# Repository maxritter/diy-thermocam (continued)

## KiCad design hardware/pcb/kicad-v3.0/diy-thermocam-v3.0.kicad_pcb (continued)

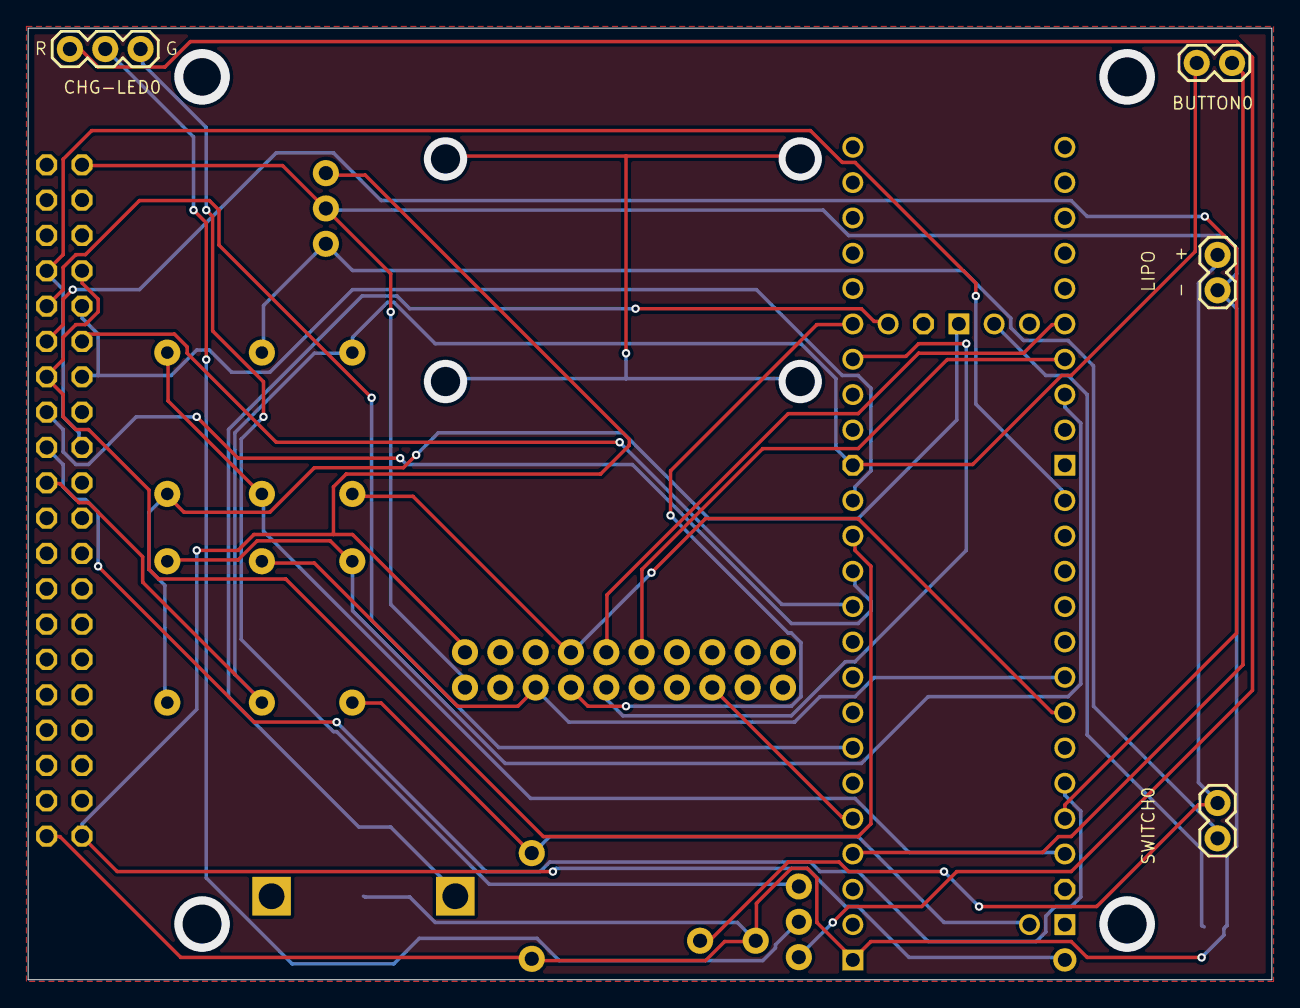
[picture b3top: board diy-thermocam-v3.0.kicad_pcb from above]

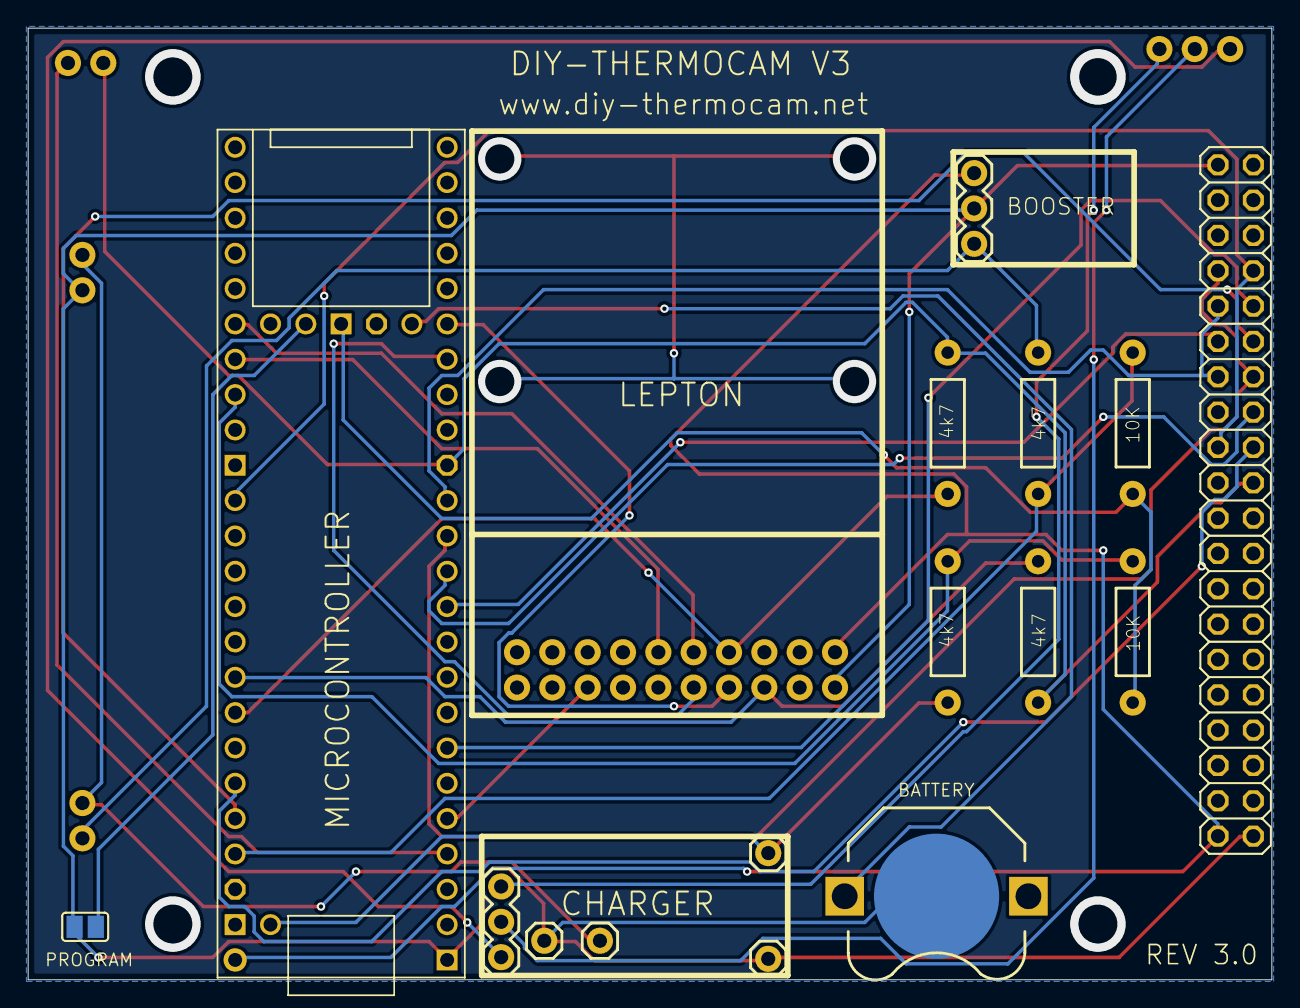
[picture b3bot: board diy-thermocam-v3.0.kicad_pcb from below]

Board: 2 copper layers, 89.4 x 68.4 mm, 21 parts (16 on the bottom side), 30 nets.

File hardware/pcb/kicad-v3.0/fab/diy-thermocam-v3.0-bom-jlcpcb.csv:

Comment,Designator,Footprint,LCSC Part #
BATTCON_12MM_PTH,BAT0,BATTCON_12MM_PTH,
1X03,BOOSTER0,1X03,
M02PTH,BUTTON0,1X02,
M02PTH,BUTTON1,1X02,
1X03,CHG-LED0,1X03,
2X10_NOSILK,J2,2X10_NOSILK,
M01PTH,JP1,1X01,
M01PTH,"JP2,JP3,JP4",1X01,
1X03,LASER1,1X03,
2X20,LCD-HEADER0,2X20,
SJ,PROGRAM0,SJ,
4k7,"R1,R3,R4,R6",AXIAL-0.4,
10K,"R2,R5",AXIAL-0.4,
M02PTH,SWITCH0,1X02,
TEENSY41-E,U$2,TENNSY41-E,C2337

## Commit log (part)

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2021-06-26 Inner.png: added
2021-06-26 index.md: updated image in sections
2021-06-26 Inner_Trans.png: added
2021-06-26 index.md: updated content in sections
2021-06-26 index.md: changed
2021-06-26 thermal-images.md: updated content in sections
2021-06-26 index.md: updated title in seo
2021-06-26 index.md: updated description in seo
2021-06-26 index.md: updated value in extra
2021-06-26 build-your-own.md: updated markdown_content
2021-06-27 manual.md: added. docs.yml: added page src/pages/docs/manual.md
2021-06-27 manual.md: changed
2021-06-27 manual.md: added
2021-06-27 manual.md: removed
2021-06-27 index.md: added
2021-06-27 usb-protocol.md: removed
2021-06-27 manual: removed
2021-06-27 site-metadata.json: updated nav_links in header
2021-06-27 site-metadata.json: updated style in nav_links
2021-06-27 site-metadata.json: updated label in nav_links
2021-06-27 site-metadata.json: updated url in nav_links
2021-06-27 site-metadata.json: updated new_window in nav_links
2021-06-27 1623780727142.jpg: added
2021-06-27 thermocam.jpg: added
2021-06-27 index.md: updated markdown_content
2021-06-27 docs.jpg: added
2021-06-27 Schematic.JPG: added
2021-06-29 Latest FW changes, still WIP
2021-06-30 Latest changes to V3 firmware - still WIP
2021-07-05 Latest changes to V3 firmware
2021-07-05 index.md: updated label in actions
2021-07-05 index.md: updated url in actions
2021-07-17 Update Teensyduino link
2021-08-04 Refresh page
2021-08-04 stackbit.yaml: Update stackbit.yaml
2021-08-20 Updating Firmware Updater Guide
2021-11-25 building-instructions.md: added. page.yml: added page src/pages/building-instructions.md
2021-11-25 building-instructions.md: added
2021-11-25 building-instructions.md: updated subtitle
2021-11-25 building-instructions.md: updated markdown_content
2021-11-25 build-your-own.md: removed. page.yml: removed page src/pages/build-your-own.md
2021-11-25 building-instructions.md: updated title
2021-11-25 software.md: updated title
2021-11-25 site-metadata.json: updated content in footer
2021-11-25 site-metadata.json: updated links in footer
2021-11-25 index.md: updated sections
2022-10-15 Added Python Source Code for Thermal Live Viewer
2023-04-28 Updated Website
2023-04-28 Fixed images
2023-04-28 Fixed SEO image
2023-04-28 Small changes
2023-05-06 Restructured Repository and General Updates
2023-05-06 Latest updates to website
2023-05-06 Bugfixes
2023-05-06 Latest changes
2023-05-07 Updated Device Firmware to 3.0.3
2023-05-07 Updated instructions for firmware flashing
2023-05-07 Small changes to index
2023-05-07 Small changes to site
2023-05-07 Updated partlist
2023-05-07 Updated Building Instructions
2023-10-20 Added support for FLIR Lepton3.1R
2024-10-23 Remove GroupGets Kit
2024-10-23 Remove year
2024-10-23 Change Title
2024-10-23 Update title
2025-02-17 Made changes to live_viewer.py and main.py SAve Video
2025-02-17 cleanup
2025-02-17 added the module in requirements list
2025-02-17 import cv2
2025-02-23 Added Comport Selection Menu and fixed a bug
2025-11-08 Added tracking
